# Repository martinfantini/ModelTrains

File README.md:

# ModelTrains

This repository contains all the necesarry information to develop an model trains mock-up

## DCC Central

Here is all the information related to the DCC central, which has a DCC booster, to have more than 2A of the output current.

## Expander

Here is the expander connected to the central, to have more input/output configuation.

## Occupancy

Here is the Ocupancy board, to know where is the train located.

## Control Program

For control all the model trains mock-up, I use the [Rocrail](https://wiki.rocrail.net/doku.php?id=start). Because
I do have the shema of the mock-up already dome.

for the future, I can test it on [JMRI](https://www.jmri.org/), because it seems more programaticlly.

## Signal

This is the DCC circuic, which sniffers the DCC signaliing and generate changes for the signals in the mock-up.

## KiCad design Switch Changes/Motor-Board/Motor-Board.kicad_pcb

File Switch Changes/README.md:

# Motor-Board

TODO

# Sniffer-Motors

TODO

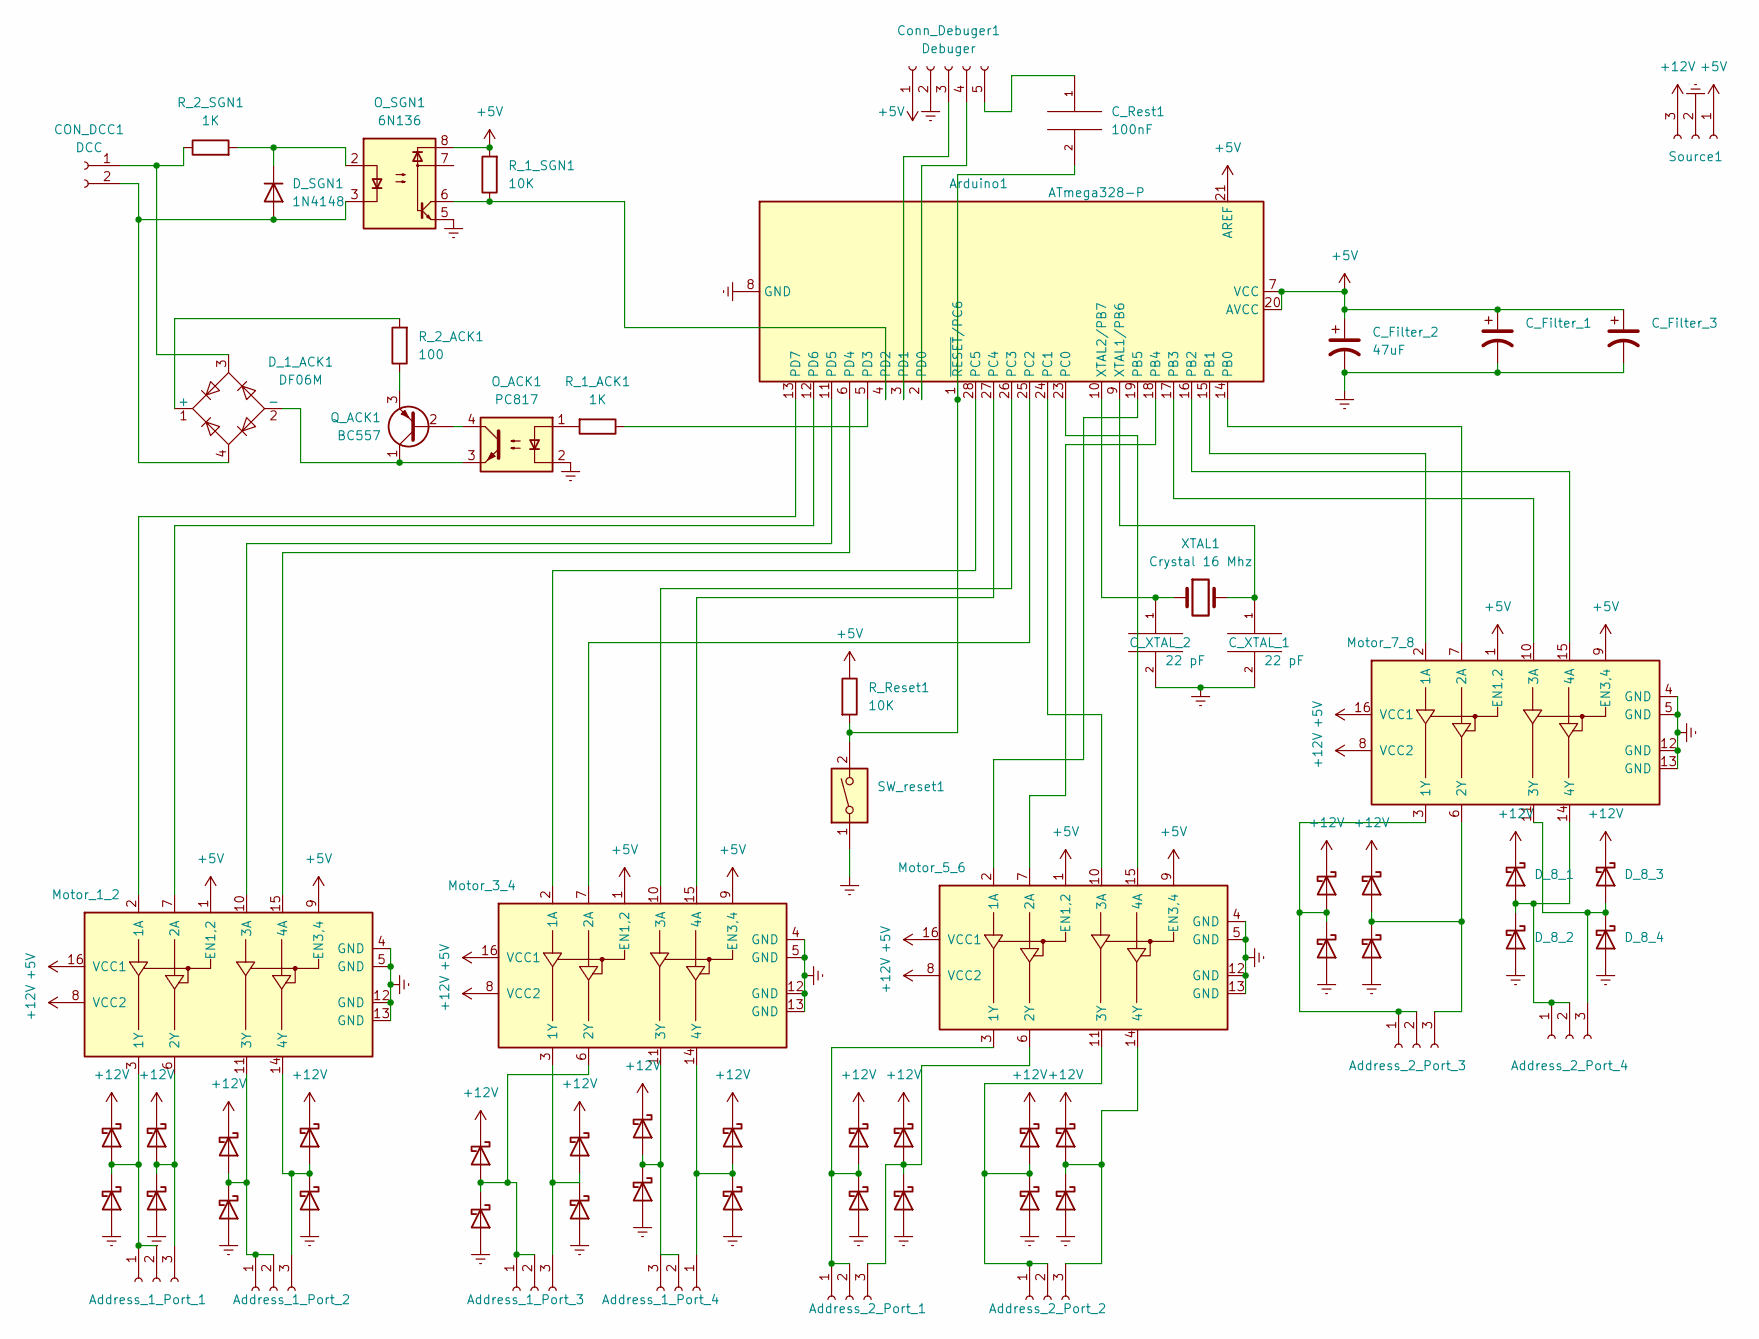
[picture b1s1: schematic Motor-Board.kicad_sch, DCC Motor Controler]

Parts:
Address_1_Port_1, Address_1_Port_2, Address_1_Port_3, Address_1_Port_4, Address_2_Port_1, Address_2_Port_2, Address_2_Port_3, Address_2_Port_4: Conn_01x03_Female; Wago_734-133_1x03_P3.50mm_Vertical
Arduino1: ATmega328-P; DIP-28_W7.62mm
CON_DCC1: DCC; Wago_734-132_1x02_P3.50mm_Vertical
C_Filter_1, C_Filter_3: (no value)
C_Filter_2: 47uF; CP_Radial_D8.0mm_P3.80mm
C_Rest1: 100nF; C_2225_5664Metric_Pad1.80x6.60mm_HandSolder
C_XTAL_1, C_XTAL_2: 22 pF; C_Disc_D8.0mm_W5.0mm_P5.00mm
Conn_Debuger1: Debuger; PinHeader_1x05_P2.54mm_Vertical
D_1_1, D_1_2, D_1_3, D_1_4, D_2_1, D_2_2, D_2_3, D_2_4, D_3_1, D_3_2, D_3_3, D_3_4, D_4_1, D_4_2, D_4_3, D_4_4, D_5_1, D_5_2, D_5_3, D_5_4, D_6_1, D_6_2, D_6_3, D_6_4, D_7_1, D_7_2, D_7_3, D_7_4, D_8_1, D_8_2, D_8_3, D_8_4: 1N5819; D_DO-41_SOD81_P10.16mm_Horizontal
D_1_ACK1: DF06M; Diode_Bridge_DIP-4_W7.62mm_P5.08mm
D_SGN1: 1N4148; D_DO-35_SOD27_P7.62mm_Horizontal
Motor_1_2, Motor_3_4, Motor_5_6, Motor_7_8: L293; DIP-16_W7.62mm
O_ACK1: PC817; DIP-4_W7.62mm
O_SGN1: 6N136; DIP-8_W7.62mm
Q_ACK1: BC557; TO-92_Inline
R_1_ACK1, R_2_SGN1: 1K; R_Axial_DIN0207_L6.3mm_D2.5mm_P10.16mm_Horizontal
R_1_SGN1: 10K; R_Axial_DIN0207_L6.3mm_D2.5mm_P10.16mm_Horizontal
R_2_ACK1: 100; R_Axial_DIN0207_L6.3mm_D2.5mm_P10.16mm_Horizontal
R_Reset1: 10K; R_Axial_DIN0207_L6.3mm_D2.5mm_P10.16mm_Horizontal
SW_reset1: (no value)
Source1: Source; JST_NV_B03P-NV_1x03_P5.00mm_Vertical
XTAL1: Crystal 16 Mhz; Crystal_HC49-U_Vertical

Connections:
+5V: Arduino1.7 (VCC), Arduino1.20 (AVCC), Arduino1.21 (AREF), C_Filter_1.1, C_Filter_2.1, C_Filter_3.1, Conn_Debuger1.1, Motor_1_2.1 (EN1,2), Motor_1_2.9 (EN3,4), Motor_1_2.16 (VCC1), Motor_3_4.1 (EN1,2), Motor_3_4.9 (EN3,4), Motor_3_4.16 (VCC1), Motor_5_6.1 (EN1,2), Motor_5_6.9 (EN3,4), Motor_5_6.16 (VCC1), Motor_7_8.1 (EN1,2), Motor_7_8.9 (EN3,4), Motor_7_8.16 (VCC1), O_SGN1.8, R_1_SGN1.2, R_Reset1.1, Source1.1
+12V: D_1_1.1 (K), D_1_3.1 (K), D_2_1.1 (K), D_2_3.1 (K), D_3_1.1 (K), D_3_3.1 (K), D_4_1.1 (K), D_4_3.1 (K), D_5_1.1 (K), D_5_3.1 (K), D_6_1.1 (K), D_6_3.1 (K), D_7_1.1 (K), D_7_3.1 (K), D_8_1.1 (K), D_8_3.1 (K), Motor_1_2.8 (VCC2), Motor_3_4.8 (VCC2), Motor_5_6.8 (VCC2), Motor_7_8.8 (VCC2), Source1.3
Earth: Arduino1.8 (GND), Arduino1.22 (GND), C_Filter_1.2, C_Filter_2.2, C_Filter_3.2, C_XTAL_1.2, C_XTAL_2.2, Conn_Debuger1.2, D_1_2.2 (A), D_1_4.2 (A), D_2_2.2 (A), D_2_4.2 (A), D_3_2.2 (A), D_3_4.2 (A), D_4_2.2 (A), D_4_4.2 (A), D_5_2.2 (A), D_5_4.2 (A), D_6_2.2 (A), D_6_4.2 (A), D_7_2.2 (A), D_7_4.2 (A), D_8_2.2 (A), D_8_4.2 (A), Motor_1_2.4 (GND), Motor_1_2.5 (GND), Motor_1_2.12 (GND), Motor_1_2.13 (GND), Motor_3_4.4 (GND), Motor_3_4.5 (GND), Motor_3_4.12 (GND), Motor_3_4.13 (GND), Motor_5_6.4 (GND), Motor_5_6.5 (GND), Motor_5_6.12 (GND), Motor_5_6.13 (GND), Motor_7_8.4 (GND), Motor_7_8.5 (GND), Motor_7_8.12 (GND), Motor_7_8.13 (GND), O_ACK1.2, O_SGN1.5, SW_reset1.1, Source1.2
unnamed: Address_1_Port_1.1, Address_1_Port_1.2, D_1_1.2 (A), D_1_2.1 (K), Motor_1_2.3 (1Y)
unnamed: Address_1_Port_1.3, D_1_3.2 (A), D_1_4.1 (K), Motor_1_2.6 (2Y)
unnamed: Address_1_Port_2.1, Address_1_Port_2.2, D_2_1.2 (A), D_2_2.1 (K), Motor_1_2.11 (3Y)
unnamed: Address_1_Port_2.3, D_2_3.2 (A), D_2_4.1 (K), Motor_1_2.14 (4Y)
unnamed: Address_1_Port_3.1, Address_1_Port_3.2, D_3_1.2 (A), D_3_2.1 (K), Motor_3_4.6 (2Y)
unnamed: Address_1_Port_3.3, D_3_3.2 (A), D_3_4.1 (K), Motor_3_4.3 (1Y)
unnamed: Address_1_Port_4.1, D_4_3.2 (A), D_4_4.1 (K), Motor_3_4.14 (4Y)
unnamed: Address_1_Port_4.2, Address_1_Port_4.3, D_4_1.2 (A), D_4_2.1 (K), Motor_3_4.11 (3Y)
unnamed: Address_2_Port_1.1, Address_2_Port_1.2, D_5_1.2 (A), D_5_2.1 (K), Motor_5_6.3 (1Y)
unnamed: Address_2_Port_1.3, D_5_3.2 (A), D_5_4.1 (K), Motor_5_6.6 (2Y)
unnamed: Address_2_Port_2.1, Address_2_Port_2.2, D_6_1.2 (A), D_6_2.1 (K), Motor_5_6.11 (3Y)
unnamed: Address_2_Port_2.3, D_6_3.2 (A), D_6_4.1 (K), Motor_5_6.14 (4Y)
unnamed: Address_2_Port_3.1, Address_2_Port_3.2, D_7_1.2 (A), D_7_2.1 (K), Motor_7_8.3 (1Y)
unnamed: Address_2_Port_3.3, D_7_3.2 (A), D_7_4.1 (K), Motor_7_8.6 (2Y)
unnamed: Address_2_Port_4.1, Address_2_Port_4.2, D_8_1.2 (A), D_8_2.1 (K), Motor_7_8.14 (4Y)
unnamed: Address_2_Port_4.3, D_8_3.2 (A), D_8_4.1 (K), Motor_7_8.11 (3Y)
unnamed: Arduino1.1 (~RESET/PC6), C_Rest1.2, R_Reset1.2, SW_reset1.2
unnamed: Arduino1.2 (PD0), Conn_Debuger1.4
unnamed: Arduino1.3 (PD1), Conn_Debuger1.3
unnamed: Arduino1.4 (PD2), O_SGN1.6, R_1_SGN1.1
unnamed: Arduino1.5 (PD3), R_1_ACK1.1
unnamed: Arduino1.6 (PD4), Motor_1_2.15 (4A)
unnamed: Arduino1.9 (XTAL1/PB6), C_XTAL_1.1, XTAL1.2
unnamed: Arduino1.10 (XTAL2/PB7), C_XTAL_2.1, XTAL1.1
unnamed: Arduino1.11 (PD5), Motor_1_2.10 (3A)
unnamed: Arduino1.12 (PD6), Motor_1_2.7 (2A)
unnamed: Arduino1.13 (PD7), Motor_1_2.2 (1A)
unnamed: Arduino1.14 (PB0), Motor_7_8.7 (2A)
unnamed: Arduino1.15 (PB1), Motor_7_8.2 (1A)
unnamed: Arduino1.16 (PB2), Motor_7_8.15 (4A)
unnamed: Arduino1.17 (PB3), Motor_7_8.10 (3A)
unnamed: Arduino1.18 (PB4), Motor_5_6.7 (2A)
unnamed: Arduino1.19 (PB5), Motor_5_6.2 (1A)
unnamed: Arduino1.23 (PC0), Motor_5_6.15 (4A)
unnamed: Arduino1.24 (PC1), Motor_5_6.10 (3A)
unnamed: Arduino1.25 (PC2), Motor_3_4.7 (2A)
unnamed: Arduino1.26 (PC3), Motor_3_4.10 (3A)
unnamed: Arduino1.27 (PC4), Motor_3_4.15 (4A)
unnamed: Arduino1.28 (PC5), Motor_3_4.2 (1A)
unnamed: CON_DCC1.1, D_1_ACK1.3, R_2_SGN1.1
unnamed: CON_DCC1.2, D_1_ACK1.4, D_SGN1.2 (A), O_SGN1.3
unnamed: C_Rest1.1, Conn_Debuger1.5
unnamed: D_1_ACK1.1 (+), R_2_ACK1.2
unnamed: D_1_ACK1.2 (-), O_ACK1.3, Q_ACK1.1 (C)
unnamed: D_SGN1.1 (K), O_SGN1.2, R_2_SGN1.2
unnamed: O_ACK1.1, R_1_ACK1.2
unnamed: O_ACK1.4, Q_ACK1.2 (B)
unnamed: Q_ACK1.3 (E), R_2_ACK1.1

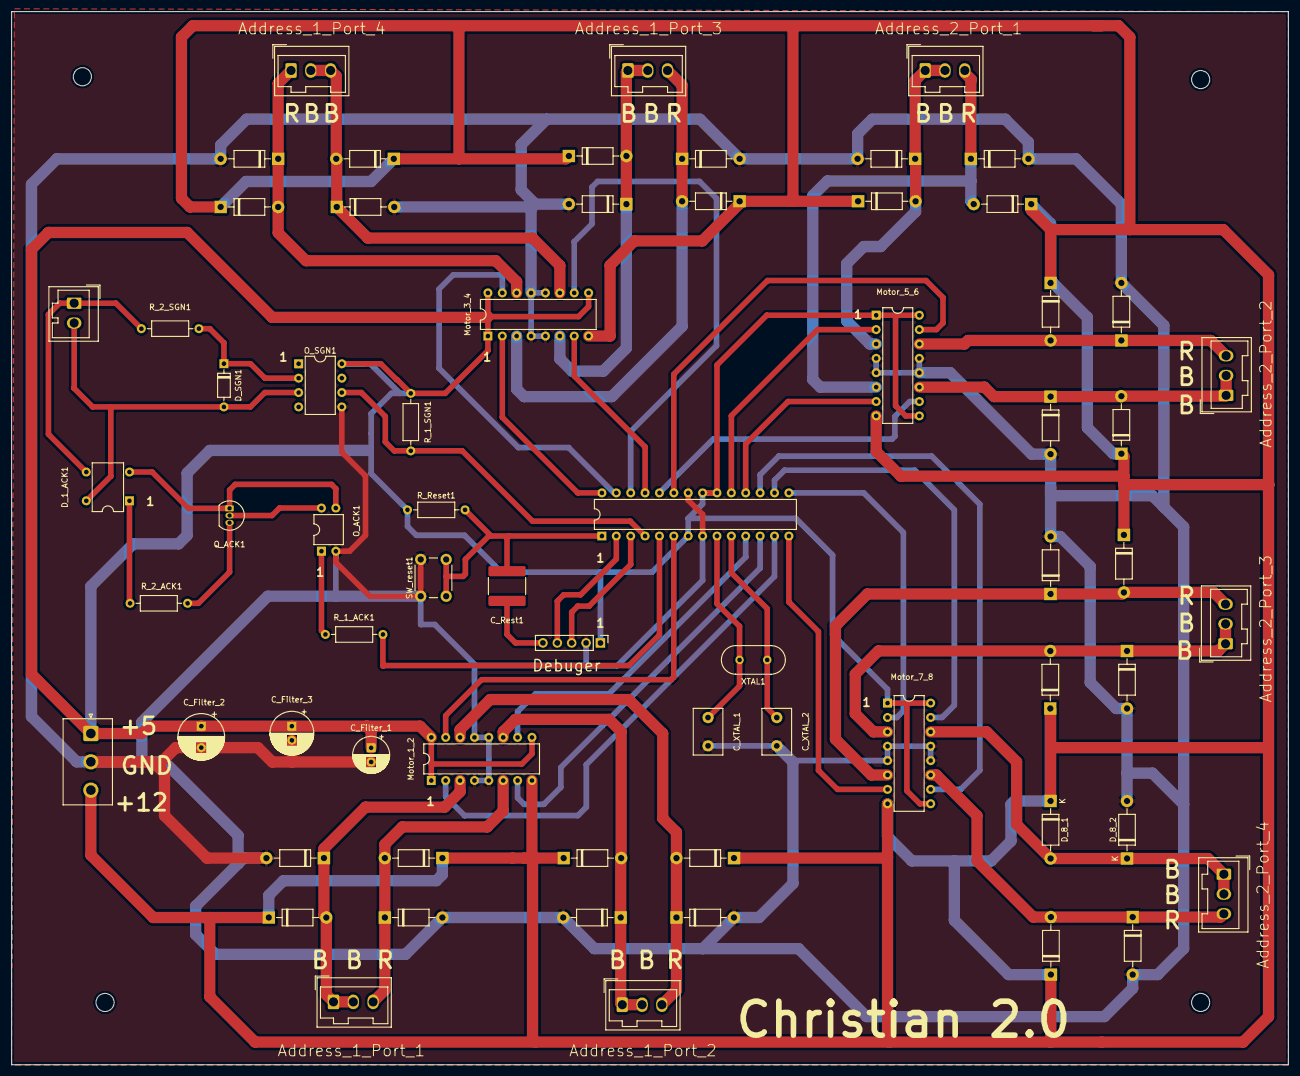
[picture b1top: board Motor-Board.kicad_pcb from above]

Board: 2 copper layers, 225.5 x 186.0 mm, 66 parts (0 on the bottom side), 51 nets.

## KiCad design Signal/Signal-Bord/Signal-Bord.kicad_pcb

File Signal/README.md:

# Signal-Board

The board is designed with the Arduino Nano as a prototype. And the final design with Atmega328p which is the same in Arduino Nano Board.
The signals, which I use have 4 aspects, which are defined in the next enumeration outputs:

```c++
#define CON_1_PIN_R 4   // Pin 6  - PD4
#define CON_1_PIN_G 5   // Pin 11 - PD5
#define CON_1_PIN_Y 6   // Pin 12 - PD6
#define CON_1_PIN_O 7   // Pin 13 - PD7

#define CON_2_PIN_R 8   // Pin 14 - PB0
#define CON_2_PIN_G 9   // Pin 15 - PB1
#define CON_2_PIN_Y 10  // Pin 16 - PB2
#define CON_2_PIN_O 11  // Pin 17 - PB3

#define CON_3_PIN_R A5  // Pin 28 - PC5
#define CON_3_PIN_G A4  // Pin 27 - PC4
#define CON_3_PIN_Y A3  // Pin 26 - PC3
#define CON_3_PIN_O A2  // Pin 25 - PC1

#define CON_4_PIN_R A1  // Pin 24 - PD7
#define CON_4_PIN_G A0  // Pin 23 - PC0
#define CON_4_PIN_Y 13  // Pin 19 - PB5
#define CON_4_PIN_O 12  // Pin 18 - PB4PD7
```

and the DCC information, it takes from the pins:

```c++
#define DCC_ACK_SIGNAL 3  // Pin 5 - PD3
#define DCC_PIN_IN     2  // Pin 4 - PD2
```

# Sniffer-Signal

As arduino offers, it is programed in C++.
For the case od the DCC protocol, I it is used PADA (Port Accessory Decoder Address) configuration. Which means the next default configuration will be the one which makes the signals on:

```
Connector 1:
Address = <Address_1> ; Port = <Port_1> ; Gate = 0 ; ==> Aspect: Red
Address = <Address_1> ; Port = <Port_1> ; Gate = 1 ; ==> Aspect: Green
Address = <Address_1> ; Port = <Port_2> ; Gate = 0 ; ==> Aspect: Yellow
Address = <Address_1> ; Port = <Port_2> ; Gate = 1 ; ==> Aspect: Orange
```

```
Connector 2:
Address = <Address_1> ; Port = <Port_3> ; Gate = 0 ; ==> Aspect: Red
Address = <Address_1> ; Port = <Port_3> ; Gate = 1 ; ==> Aspect: Green
Address = <Address_1> ; Port = <Port_4> ; Gate = 0 ; ==> Aspect: Yellow
Address = <Address_1> ; Port = <Port_4> ; Gate = 1 ; ==> Aspect: Orange
```

```
Connector 3:
Address = <Address_2> ; Port = <Port_1> ; Gate = 0 ; ==> Aspect: Red
Address = <Address_2> ; Port = <Port_1> ; Gate = 1 ; ==> Aspect: Green
Address = <Address_2> ; Port = <Port_2> ; Gate = 0 ; ==> Aspect: Yellow
Address = <Address_2> ; Port = <Port_2> ; Gate = 1 ; ==> Aspect: Orange
```

```
Connector 4:
Address = <Address_2> ; Port = <Port_3> ; Gate = 0 ; ==> Aspect: Red
Address = <Address_2> ; Port = <Port_3> ; Gate = 1 ; ==> Aspect: Green
Address = <Address_2> ; Port = <Port_4> ; Gate = 0 ; ==> Aspect: Yellow
Address = <Address_2> ; Port = <Port_4> ; Gate = 1 ; ==> Aspect: Orange
```

And here are the DCC programming commands (Observation: it has to be in the programming track to make it work) are:

* For the case the default configuration, you have to send:

```
DCC Command: 8; Value = 0
```

* Address configuration

```
DCC Command: 37; Value = Address_1
DCC Command: 38; Value = Address_2
```

* Addressing Mode: Only allowed the PADA, until now.

```
DCC Command: 39; Value = 1
```

The possible values are:
```
Pada = 1
Fada = 2
```

Observation: The Fada (Flat Accessory Decoder Address) mode is not sported.

* Set the values on start-up, to set the values on start up, you can do with the commands:

```
DCC Command: 40; Value = 0
DCC Command: 42; Value = 0
```

The definition is:

For the DCC command 40, it covers:

```
Bits: x1-x2-x3-x4-x5-x6-x7-x8
    * x1-x2-x3-x4: Values associated to the connector 2
    * x5-x6-x7-x8: Values associated to the connector 1
```

For the DCC command 42, it covers:

```
Bits: x1-x2-x3-x4-x5-x6-x7-x8
    * x1-x2-x3-x4: Values associated to the connector 4
    * x5-x6-x7-x8: Values associated to the connector 3
```

* Define a blinking frequency:

```
DCC Command: 48; Value = 1
```

This frequency is set in seconds.

* Configure output for blinking:

```
Bits Value: y4-y3-y2-y1 x4-x3-x2-x1
    * y4-y3-y2-y1: which is the output has to blink
    * x4-x3-x2-x1: which of the 4 has to blink:
Example:
    * 0001 0010: Here will blink with the Port 1, the output G and the output R will be on.
    * 1001 0010: Here will blink with the Port 1 and Port 4, the output G and the output R will be on.
```

And the configuration are:

```
DCC Command: 44; Value = 0
DCC Command: 45; Value = 0
DCC Command: 46; Value = 0
DCC Command: 47; Value = 0
```

* Configure which output goes on, with which command:

The configuration for the four states is:

```
Default connector values
CV_CONNECTOR_X_COMMAND_1_2 = y4-y3-y2-y1 x4-x3-x2-x1 = 0x84
- Aspect 1: RGY0 XXXX = y4-y3-y2-y1
- Aspect 2: XXXX RGY0 = x4-x3-x2-x1
CV_CONNECTOR_X_COMMAND_3_4 = y4-y3-y2-y1 x4-x3-x2-x1 = 0x84
- Aspect 3: RGY0 XXXX = y4-y3-y2-y1
- Aspect 4: XXXX RGY0 = x4-x3-x2-x1
```

and the default definition is:

```c++
DCC Command: 49; Value = 0x84 // CV_CONNECTOR_1_COMMAND_1_2
DCC Command: 50; Value = 0x21 // CV_CONNECTOR_1_COMMAND_3_4
DCC Command: 51; Value = 0x84 // CV_CONNECTOR_2_COMMAND_1_2
DCC Command: 52; Value = 0x21 // CV_CONNECTOR_2_COMMAND_3_4
DCC Command: 53; Value = 0x84 // CV_CONNECTOR_3_COMMAND_1_2
DCC Command: 54; Value = 0x21 // CV_CONNECTOR_3_COMMAND_3_4
DCC Command: 55; Value = 0x84 // CV_CONNECTOR_4_COMMAND_1_2
DCC Command: 56; Value = 0x21 // CV_CONNECTOR_4_COMMAND_3_4
```

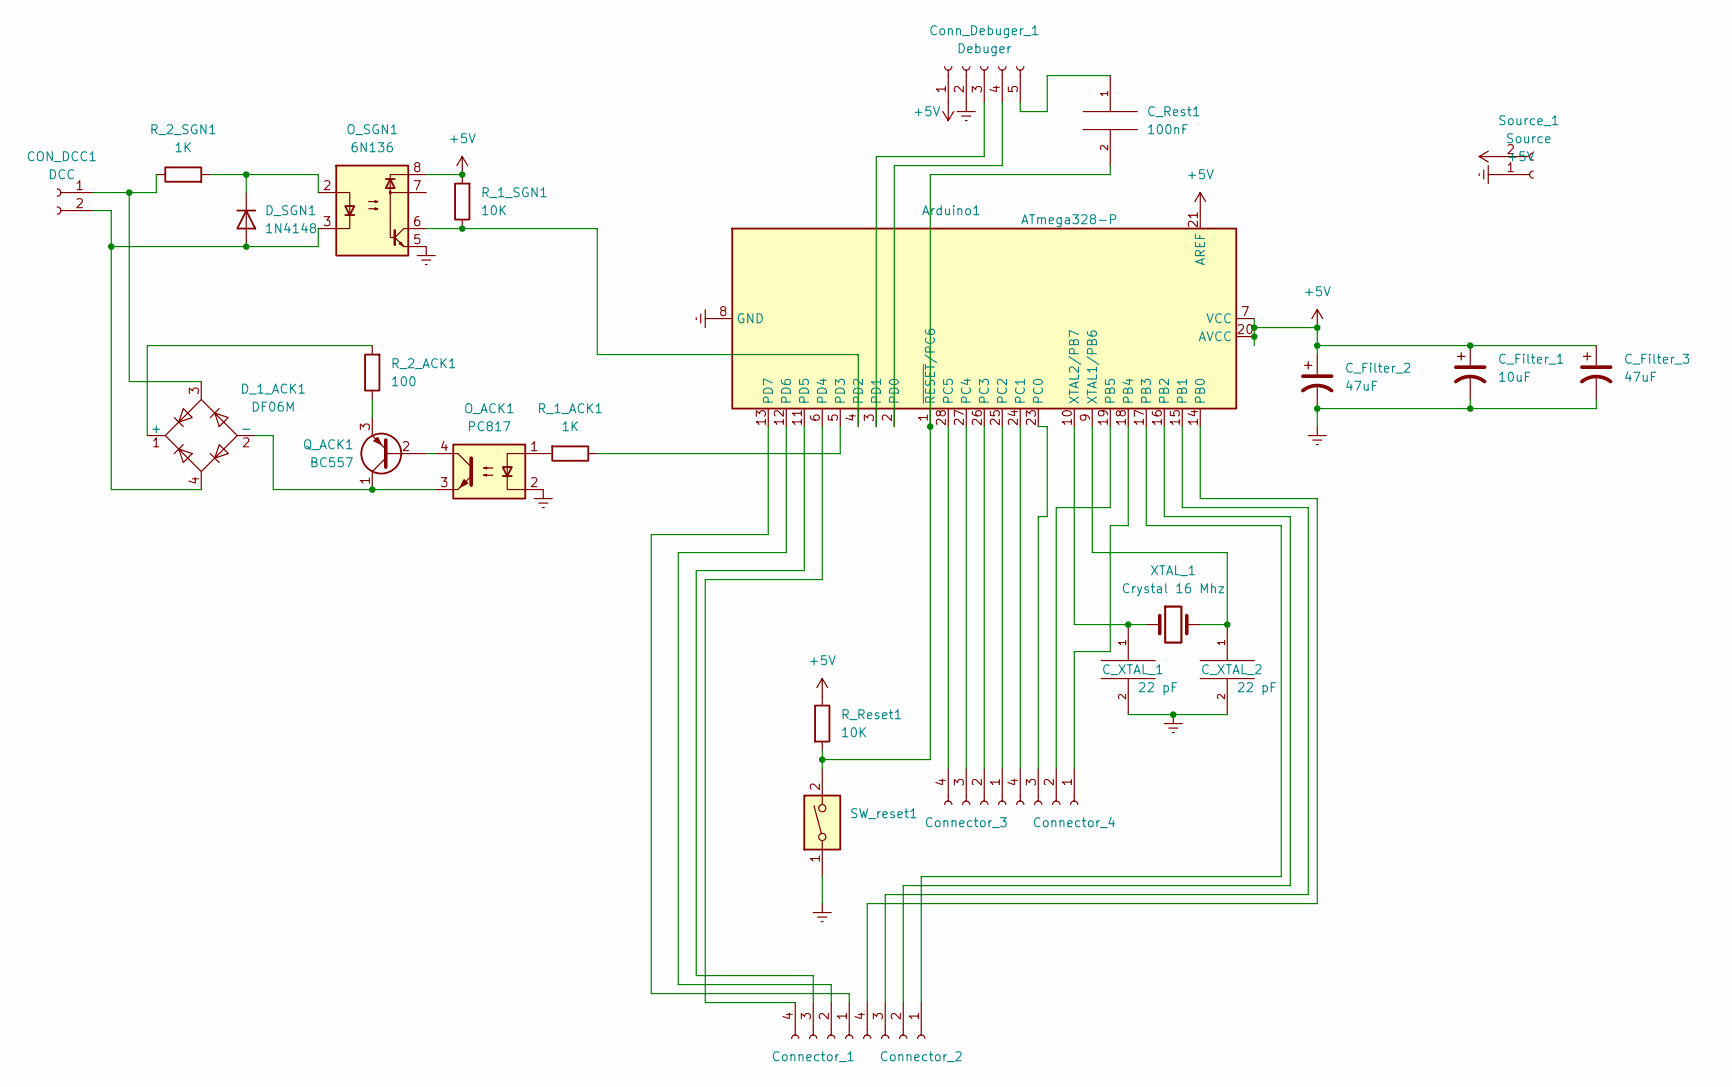
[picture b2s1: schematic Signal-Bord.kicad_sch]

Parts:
Arduino1: ATmega328-P; DIP-28_W7.62mm
CON_DCC1: DCC; Wago_734-132_1x02_P3.50mm_Vertical
C_Filter_1: 10uF; CP_Radial_D6.3mm_P2.50mm
C_Filter_2: 47uF; CP_Radial_D8.0mm_P3.80mm
C_Filter_3: 47uF; CP_Radial_D7.5mm_P2.50mm
C_Rest1: 100nF; C_2225_5664Metric_Pad1.80x6.60mm_HandSolder
C_XTAL_1, C_XTAL_2: 22 pF; C_Disc_D8.0mm_W5.0mm_P5.00mm
Conn_Debuger_1: Debuger; PinHeader_1x05_P2.54mm_Vertical
Connector_1, Connector_2, Connector_3, Connector_4: Conn_01x04_Female; Wago_734-134_1x04_P3.50mm_Vertical
D_1_ACK1: DF06M; Diode_Bridge_DIP-4_W7.62mm_P5.08mm
D_SGN1: 1N4148; D_DO-35_SOD27_P7.62mm_Horizontal
O_ACK1: PC817; DIP-4_W7.62mm
O_SGN1: 6N136; DIP-8_W7.62mm
Q_ACK1: BC557; TO-92_Inline
R_1_ACK1, R_2_SGN1: 1K; R_Axial_DIN0207_L6.3mm_D2.5mm_P10.16mm_Horizontal
R_1_SGN1: 10K; R_Axial_DIN0207_L6.3mm_D2.5mm_P10.16mm_Horizontal
R_2_ACK1: 100; R_Axial_DIN0207_L6.3mm_D2.5mm_P10.16mm_Horizontal
R_Reset1: 10K; R_Axial_DIN0207_L6.3mm_D2.5mm_P10.16mm_Horizontal
SW_reset1: SW_DIP_x01; SW_PUSH_6mm_H5mm
Source_1: Source; JST_NV_B02P-NV_1x02_P5.00mm_Vertical
XTAL_1: Crystal 16 Mhz; Crystal_HC49-U_Vertical

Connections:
+5V: Arduino1.7 (VCC), Arduino1.20 (AVCC), Arduino1.21 (AREF), C_Filter_1.1, C_Filter_2.1, C_Filter_3.1, Conn_Debuger_1.1, O_SGN1.8, R_1_SGN1.2, R_Reset1.1, Source_1.2
Earth: Arduino1.8 (GND), Arduino1.22 (GND), C_Filter_1.2, C_Filter_2.2, C_Filter_3.2, C_XTAL_1.2, C_XTAL_2.2, Conn_Debuger_1.2, O_ACK1.2, O_SGN1.5, SW_reset1.1, Source_1.1
unnamed: Arduino1.1 (~RESET/PC6), C_Rest1.2, R_Reset1.2, SW_reset1.2
unnamed: Arduino1.2 (PD0), Conn_Debuger_1.4
unnamed: Arduino1.3 (PD1), Conn_Debuger_1.3
unnamed: Arduino1.4 (PD2), O_SGN1.6, R_1_SGN1.1
unnamed: Arduino1.5 (PD3), R_1_ACK1.1
unnamed: Arduino1.6 (PD4), Connector_1.4
unnamed: Arduino1.9 (XTAL1/PB6), C_XTAL_2.1, XTAL_1.2
unnamed: Arduino1.10 (XTAL2/PB7), C_XTAL_1.1, XTAL_1.1
unnamed: Arduino1.11 (PD5), Connector_1.3
unnamed: Arduino1.12 (PD6), Connector_1.2
unnamed: Arduino1.13 (PD7), Connector_1.1
unnamed: Arduino1.14 (PB0), Connector_2.4
unnamed: Arduino1.15 (PB1), Connector_2.3
unnamed: Arduino1.16 (PB2), Connector_2.2
unnamed: Arduino1.17 (PB3), Connector_2.1
unnamed: Arduino1.18 (PB4), Connector_4.1
unnamed: Arduino1.19 (PB5), Connector_4.2
unnamed: Arduino1.23 (PC0), Connector_4.3
unnamed: Arduino1.24 (PC1), Connector_4.4
unnamed: Arduino1.25 (PC2), Connector_3.1
unnamed: Arduino1.26 (PC3), Connector_3.2
unnamed: Arduino1.27 (PC4), Connector_3.3
unnamed: Arduino1.28 (PC5), Connector_3.4
unnamed: CON_DCC1.1, D_1_ACK1.3, R_2_SGN1.1
unnamed: CON_DCC1.2, D_1_ACK1.4, D_SGN1.2 (A), O_SGN1.3
unnamed: C_Rest1.1, Conn_Debuger_1.5
unnamed: D_1_ACK1.1 (+), R_2_ACK1.2
unnamed: D_1_ACK1.2 (-), O_ACK1.3, Q_ACK1.1 (C)
unnamed: D_SGN1.1 (K), O_SGN1.2, R_2_SGN1.2
unnamed: O_ACK1.1, R_1_ACK1.2
unnamed: O_ACK1.4, Q_ACK1.2 (B)
unnamed: Q_ACK1.3 (E), R_2_ACK1.1

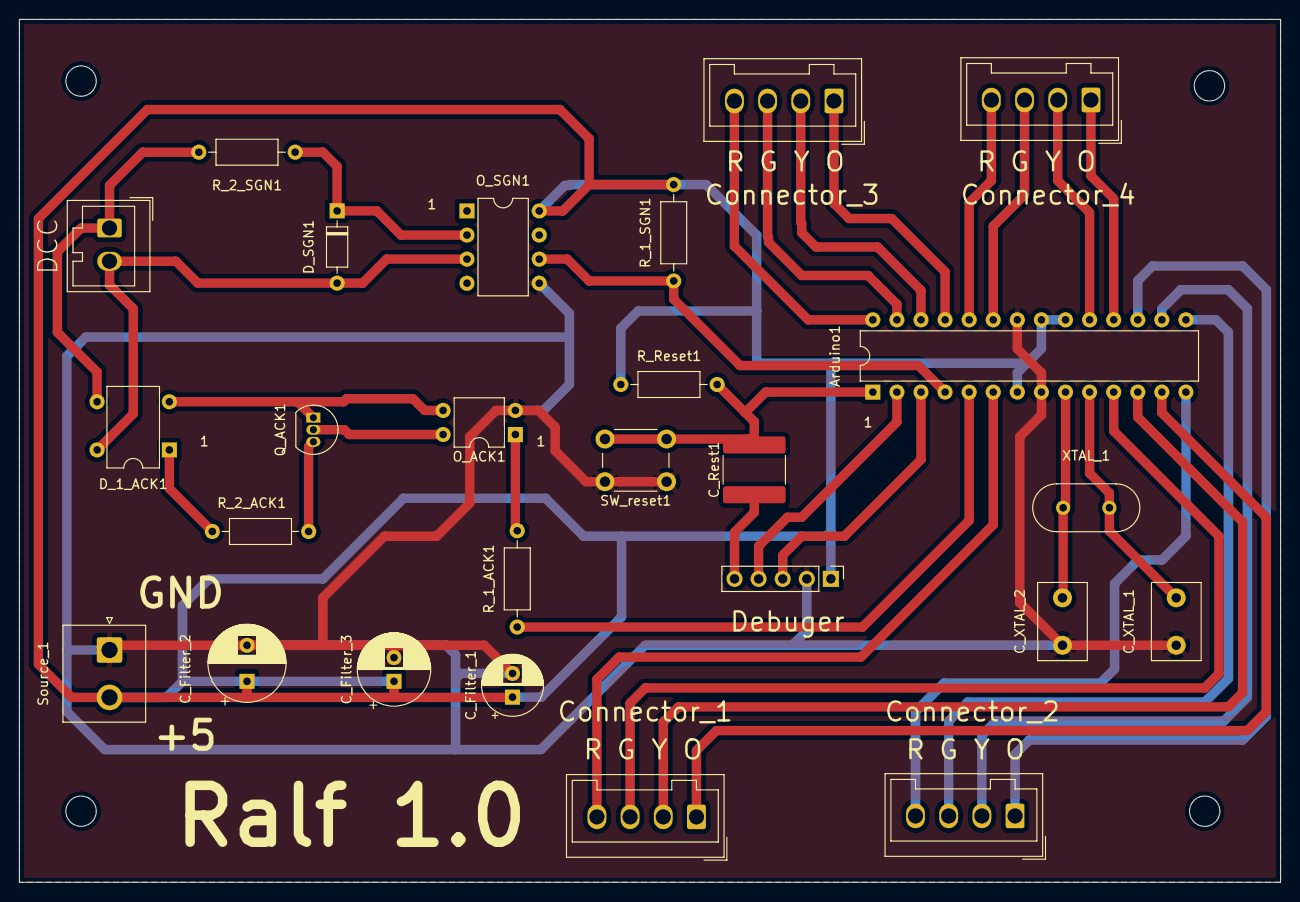
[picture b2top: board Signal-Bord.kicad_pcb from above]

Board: 2 copper layers, 133.0 x 91.0 mm, 26 parts (0 on the bottom side), 34 nets.
